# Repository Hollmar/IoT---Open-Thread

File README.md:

# IoT---Open-Thread
Projektarbeit für ein IoT - Netzwerk basierend auf der neuen von Google veröffentlichten Technologie Open Thread

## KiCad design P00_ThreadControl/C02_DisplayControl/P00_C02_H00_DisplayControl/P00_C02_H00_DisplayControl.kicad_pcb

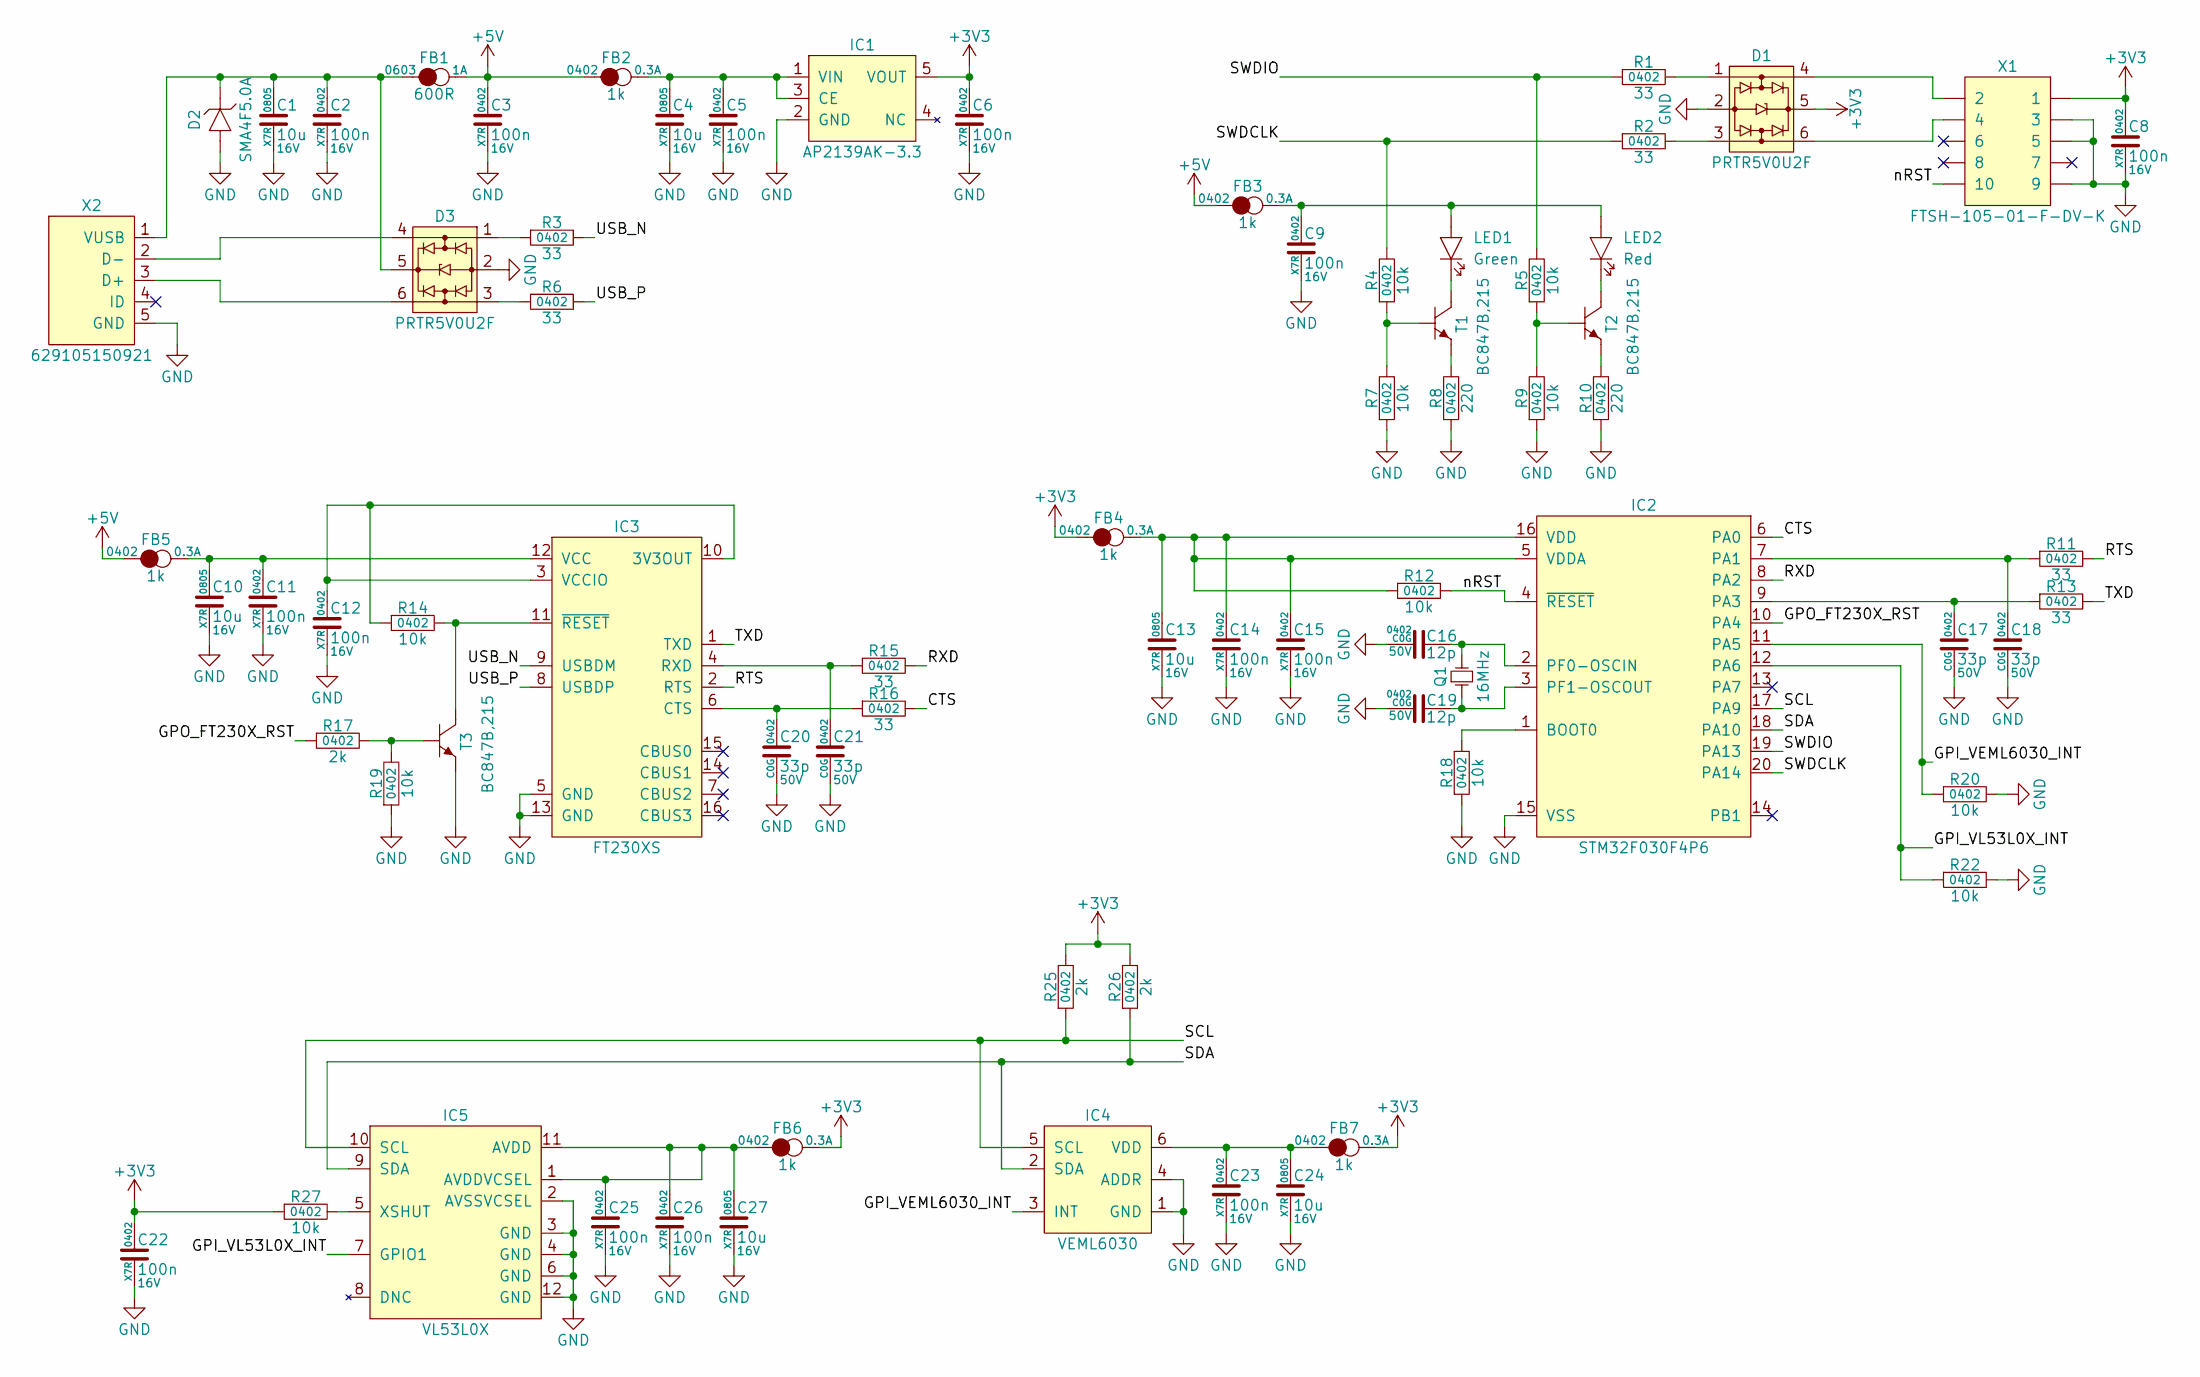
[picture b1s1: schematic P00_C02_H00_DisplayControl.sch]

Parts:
C1, C4, C10, C13, C24, C27: CL21B106KOQNNNE; C0805; Voltage 16V
C2, C3, C5, C6, C8, C9, C11, C12, C14, C15, C22, C23, C25, C26: CL05B104KO5NNNC; C0402; Voltage 16V
C16, C19: CL05C120JB5NNNC; C0402; Voltage 50V
C17, C18, C20, C21: CL05C330JB5NNNC; C0402; Voltage 50V
D1, D3: PRTR5V0U2F; SOT50P145X100X050-6_NEXPERIA_SOT886
D2: SMA4F5.0A; DIOC427X257X100_ST_DO221-AC
FB1: MPZ1608S601A; FB0603
FB2, FB3, FB4, FB5, FB6, FB7: BK1005HS102; FB0402
IC1: AP2139AK-3.3; SOT95P280X145-5
IC2: STM32F030F4P6; TSSOP065P640X650X120-20_ST
IC3: FT230XS; SOP63P600X175-16
IC4: VEML6030; VEML6030_VISHAY
IC5: VL53L0X; VL53L0X_ST
LED1: 599-0181-007F; LED0805_DIALIGHT
LED2: 599-0110-007F; LED0805_DIALIGHT
Q1: ECS-160-8-30Q-VY; ECX-53
R1, R2, R3, R6, R11, R13, R15, R16: RC0402FR-0733RL; R0402
R4, R5, R7, R9, R12, R14, R18, R19, R20, R22, R27: RC0402FR-0710KL; R0402
R8, R10: RC0402FR-07220RL; R0402
R17, R25, R26: RC0402FR-072KL; R0402
T1, T2, T3: BC847B,215; SOT95P230X100-3
X1: FTSH-105-01-F-DV-K
X2: 629105150921; 629105150921_WE

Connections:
+3V3: C6.1, C8.1, C22.1, D1.5, FB4.1, FB6.2, FB7.2, IC1.5 (VOUT), R25.2, R26.2, R27.1, X1.1
+5V: C3.1, FB1.2, FB2.1, FB3.1, FB5.1
/CTS: IC2.6 (PA0), R16.2
/GPI_VL53L0X_INT: IC2.12 (PA6), IC5.7 (GPIO1), R22.1
/GPO_FT230X_RST: IC2.10 (PA4), R17.1
/RTS: IC3.2 (RTS), R11.2
/RXD: IC2.8 (PA2), R15.2
/SCL: IC2.17 (PA9), IC4.5 (SCL), IC5.10 (SCL), R25.1
/SDA: IC2.18 (PA10), IC4.2 (SDA), IC5.9 (SDA), R26.1
/SWDCLK: IC2.20 (PA14), R2.1, R4.2
/SWDIO: IC2.19 (PA13), R1.1, R5.2
/TXD: IC3.1 (TXD), R13.2
/USB_N: IC3.9 (USBDM), R3.2
/USB_P: IC3.8 (USBDP), R6.2
/nRST: IC2.4 (~RESET), R12.2, X1.10
GND: C1.2, C2.2, C3.2, C4.2, C5.2, C6.2, C8.2, C9.2, C10.2, C11.2, C12.2, C13.2, C14.2, C15.2, C16.2, C17.2, C18.2, C19.2, C20.2, C21.2, C22.2, C23.2, C24.2, C25.2, C26.2, C27.2, D1.2, D2.1 (A), D3.2, IC1.2 (GND), IC2.15 (VSS), IC3.5 (GND), IC3.13 (GND), IC4.1 (GND), IC4.4 (ADDR), IC5.2 (AVSSVCSEL), IC5.3 (GND), IC5.4 (GND), IC5.6 (GND), IC5.12 (GND), R7.1, R8.1, R9.1, R10.1, R18.1, R19.1, R20.2, R22.2, T3.3 (C), X1.3, X1.5, X1.9, X2.5 (GND), X2.M1, X2.M2, X2.M3, X2.M4, X2.M5, X2.M6
unnamed: C1.1, C2.1, D2.2 (K), D3.5, FB1.1, X2.1 (VUSB)
unnamed: C4.1, C5.1, FB2.2, IC1.1 (VIN), IC1.3 (CE)
unnamed: C9.1, FB3.2, LED1.1 (A), LED2.1 (A)
unnamed: C10.1, C11.1, FB5.2, IC3.12 (VCC)
unnamed: C12.1, IC3.3 (VCCIO), IC3.10 (3V3OUT), R14.1
unnamed: C13.1, C14.1, C15.1, FB4.2, IC2.5 (VDDA), IC2.16 (VDD), R12.1
unnamed: C16.1, IC2.2 (PF0-OSCIN), Q1.2
unnamed: C17.1, IC2.9 (PA3), R13.1
unnamed: C18.1, IC2.7 (PA1), R11.1
unnamed: C19.1, IC2.3 (PF1-OSCOUT), Q1.1
unnamed: C20.1, IC3.6 (CTS), R16.1
unnamed: C21.1, IC3.4 (RXD), R15.1
unnamed: C23.1, C24.1, FB7.1, IC4.6 (VDD)
unnamed: C25.1, C26.1, C27.1, FB6.1, IC5.1 (AVDDVCSEL), IC5.11 (AVDD)
unnamed: D1.1, R1.2
unnamed: D1.3, R2.2
unnamed: D1.4, X1.2
unnamed: D1.6, X1.4
unnamed: D3.1, R3.1
unnamed: D3.3, R6.1
unnamed: D3.4, X2.2 (D-)
unnamed: D3.6, X2.3 (D+)
unnamed: IC2.1 (BOOT0), R18.2
unnamed: IC3.11 (~RESET), R14.2, T3.1 (B)
unnamed: IC5.5 (XSHUT), R27.2
unnamed: LED1.2 (K), T1.1 (B)
unnamed: LED2.2 (K), T2.1 (B)
unnamed: R4.1, R7.2, T1.2 (E)
unnamed: R5.1, R9.2, T2.2 (E)
unnamed: R8.2, T1.3 (C)
unnamed: R10.2, T2.3 (C)
unnamed: R17.2, R19.2, T3.2 (E)

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
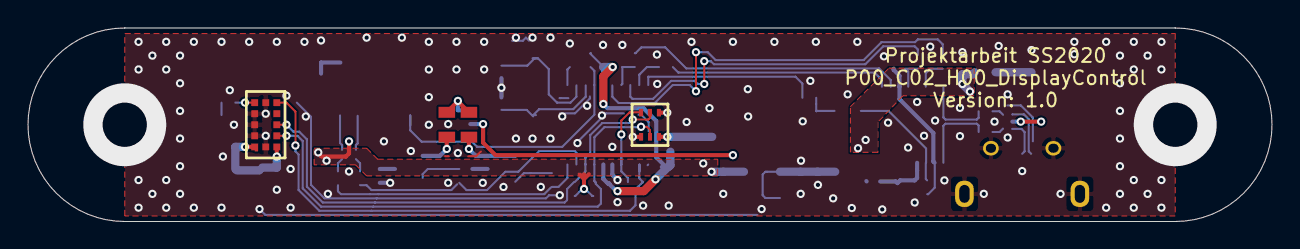
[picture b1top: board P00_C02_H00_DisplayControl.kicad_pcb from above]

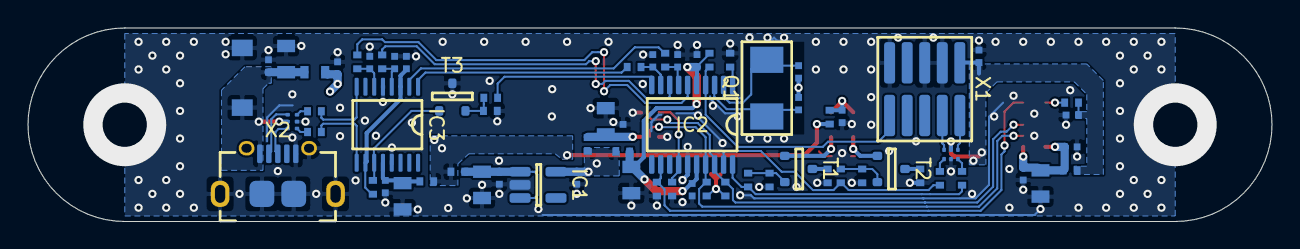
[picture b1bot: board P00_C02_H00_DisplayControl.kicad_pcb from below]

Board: 2 copper layers, 90.0 x 14.0 mm, 73 parts (69 on the bottom side), 49 nets.

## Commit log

2020-03-23 no message
2020-03-26 Added symbol for the FT230XS from FTDI.
2020-03-27 Changed naming convention from M(odule) to C(component) to allow M(echanical) parts. Added empty .gitignore file.
2020-04-14 Created all parts in our Kicad library.
2020-04-14 Created P00_C02_H00_DisplayControl PCB Version 1.0.
2020-04-17 Final PCB Version 1.0. These files where send to the manufacturer.
2020-04-17 Update library to refer to PROJEKTARBEIT relative path in KiCAD.
2020-04-20 Added manufacturer to capacitor fields in the lib.
2020-04-20 Clean project files.
